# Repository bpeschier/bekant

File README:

Inspired by gcormier/megadesk, but with dresden electronik's RFR-based module.

License
-------
This design is made available under the CERN Open Hardware License,
version 1.2 or above. See LICENSE.txt for the full text of the license.

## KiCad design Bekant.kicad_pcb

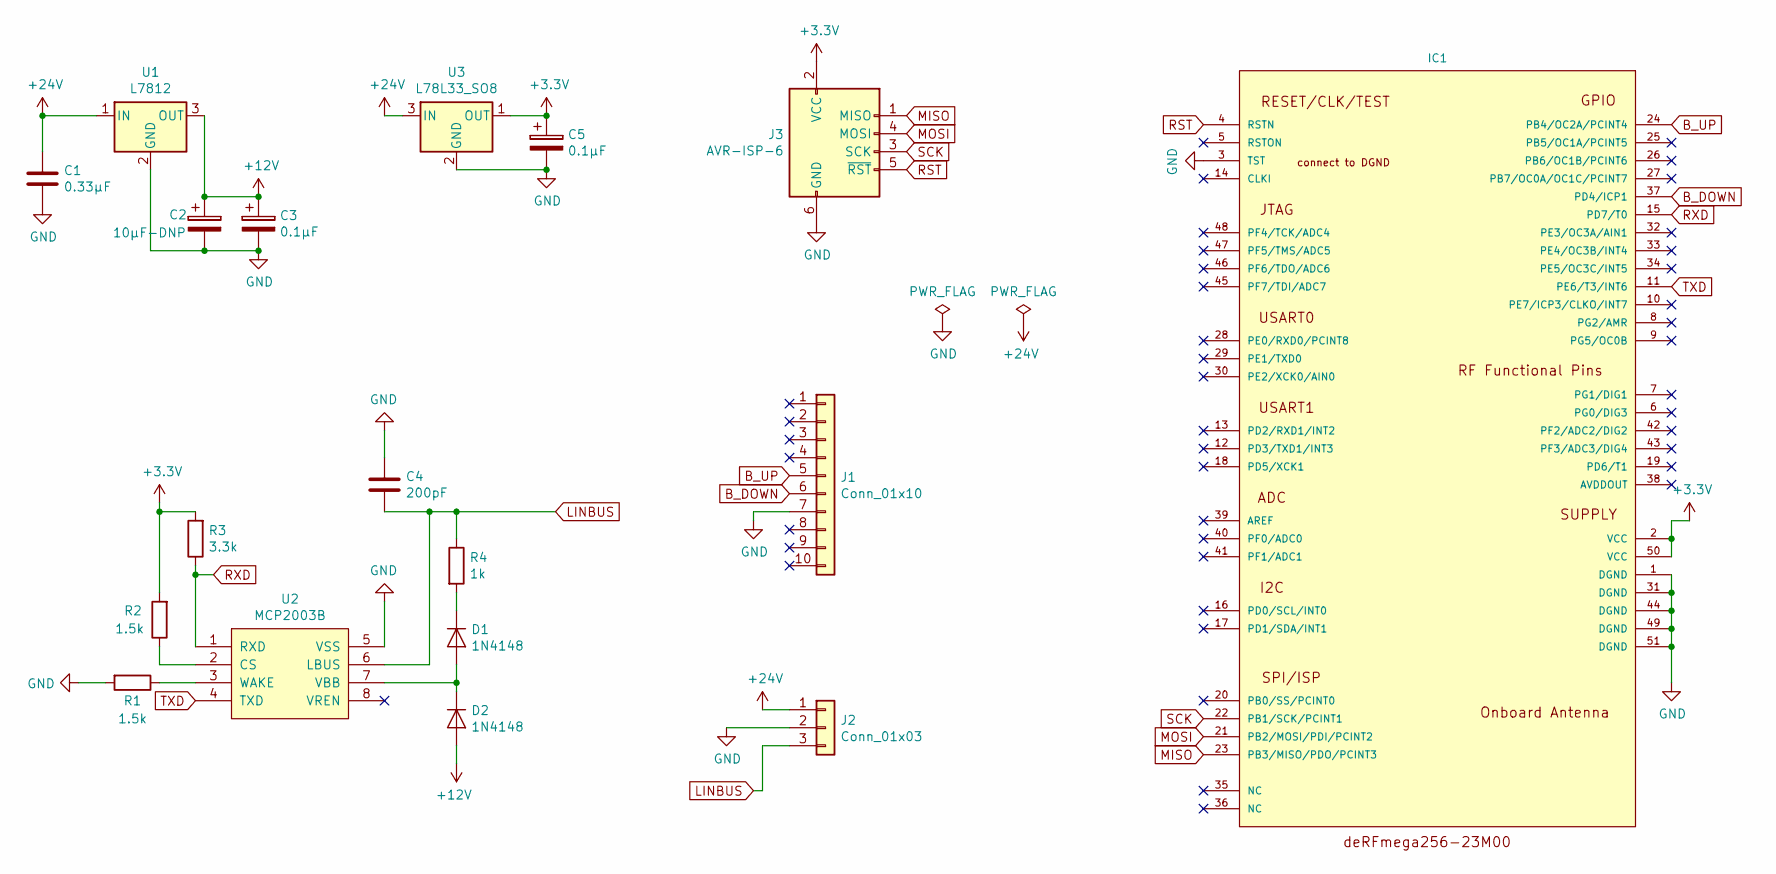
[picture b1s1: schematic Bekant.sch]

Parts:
C1: 0.33µF; C_1206_HandSoldering
C2: 10µF-DNP; C_1206_HandSoldering
C3, C5: 0.1µF; C_1206_HandSoldering
C4: 200pF; C_1206_HandSoldering
D1, D2: 1N4148; D_SOD-323_HandSoldering
IC1: DERFMEGA256-23M00; A-M00
J1: Conn_01x10; TE_84952-9_1x09-1MP_P1.0mm_Horizontal
J2: Conn_01x03; Pin_Header_Angled_1x03_Pitch2.54mm
J3: AVR-ISP-6; Pin_Header_Straight_2x03_Pitch2.54mm_SMD
R1, R2: 1.5k; R_1206_HandSoldering
R3: 3.3k; R_1206_HandSoldering
R4: 1k; R_1206_HandSoldering
U1: L7812; TO-252-3_TabPin2
U2: MCP2003B; SOIC-8_3.9x4.9mm_Pitch1.27mm
U3: L78L33_SO8; TO-252-3_TabPin2

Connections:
+3V3: C5.1, IC1.2 (VCC), IC1.50 (VCC), J3.2 (VCC), R2.2, R3.2, U3.1 (OUT); also elsewhere on the board
+12V: C2.1, C3.1, D2.2 (A), U1.3 (OUT)
+24V: C1.1, J2.1, U1.1 (IN), U3.3 (IN)
B_DOWN: IC1.37 (PD4/ICP1), J1.6
B_UP: IC1.24 (PB4/OC2A/PCINT4), J1.5
GND: C1.2, C2.2, C3.2, C4.1, C5.2, IC1.1 (DGND), IC1.3 (TST), IC1.31 (DGND), IC1.44 (DGND), IC1.49 (DGND), IC1.51 (DGND), J1.7, J2.2, J3.6 (GND), R1.2, U1.2 (GND), U2.5 (VSS), U3.2 (GND); also elsewhere on the board
LINBUS: C4.2, J2.3, R4.1, U2.6 (LBUS)
MISO: IC1.23 (PB3/MISO/PDO/PCINT3), J3.1 (MISO); also elsewhere on the board
MOSI: IC1.21 (PB2/MOSI/PDI/PCINT2), J3.4 (MOSI); also elsewhere on the board
unnamed: D1.1 (K), R4.2
unnamed: D1.2 (A), D2.1 (K), U2.7 (VBB)
unnamed: R1.1, U2.3 (WAKE)
unnamed: R2.1, U2.2 (CS)
RST: IC1.4 (RSTN), J3.5 (~RST); also elsewhere on the board
RXD: IC1.15 (PD7/T0), R3.1, U2.1 (RXD)
SCK: IC1.22 (PB1/SCK/PCINT1), J3.3 (SCK); also elsewhere on the board
TXD: IC1.11 (PE6/T3/INT6), U2.4 (TXD)

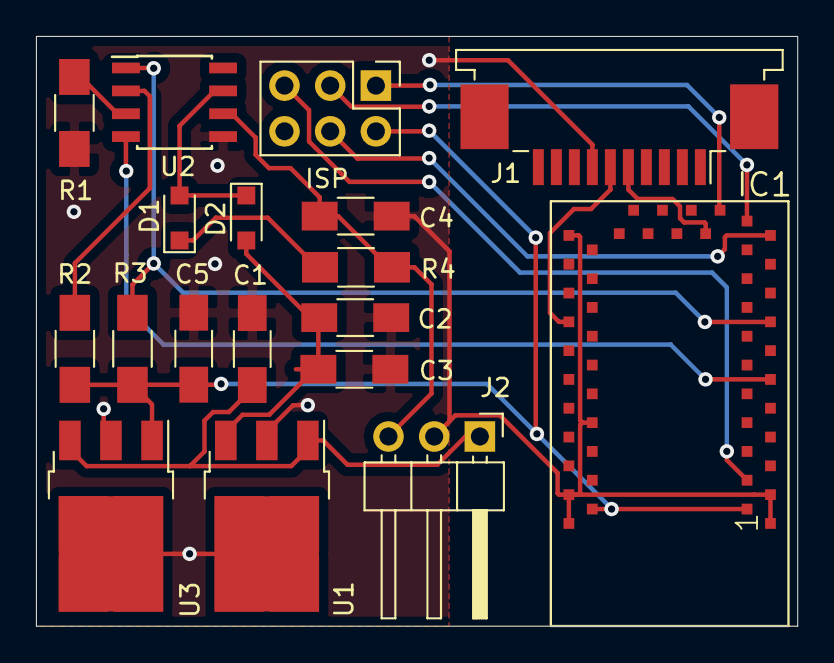
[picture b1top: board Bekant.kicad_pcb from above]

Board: 2 copper layers, 42.3 x 32.8 mm, 18 parts (0 on the bottom side), 17 nets.

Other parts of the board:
ISP: AVR-ISP-6; Pin_Header_Straight_2x03_Pitch2.54mm

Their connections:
+3V3: ISP.2; also elsewhere on the board
GND: ISP.6; also elsewhere on the board
MISO: ISP.1; also elsewhere on the board
MOSI: ISP.4; also elsewhere on the board
RST: ISP.5; also elsewhere on the board
SCK: ISP.3; also elsewhere on the board
